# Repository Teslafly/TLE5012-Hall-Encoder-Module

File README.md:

# TLE5012-Hall-Encoder-Module
Breakout/mounting board for the TLE5012 hall encoder to use with the vesc motor controller project.

(Pictures are from my nearly identical as5047 encoder board at https://github.com/Teslafly/AS5047-Hall-Encoder-Module)

# Mounting:
- The mounting holes fit an m3 screw and are 16mm apart center to center.
- If the pcb cannot recess into the motor, a 3d printed shim (file link) can raise the encoder and provide clearance. If the motor gets too hot, the shim may be laser cut or milled out of a more resistant material.
- This encoder works with a diametric magnet fixed to the motor shaft. 
    - The magnet must be centered on the shaft. The encoder must be centered over the center of the magnet.
    - I find good results with a 6x2mm or 6x3mm neodymium magnet placed 1-5mm away from the face of the encoder.
    - Magnet example: https://www.aliexpress.us/item/3256801356246959.html

# Building:
- This pcb can be hand soldered easially.
- You can use either horizontal or vertical jst gh connectors for each connector placement. The vertical data connector should be placed with pins outwards to maintain the same pinout between the horizontal/vertical data connector options.
- As the temperature sensor connector is unpolarised, either horizontal or vertical connector can be placed on the same footprint. see pictures.

# JST GH mating connectors and making cables:
- If you do not have a crimper for JST GH crimps, they are fiddley and are hard to crimp properly.
I recommend either getting a male to male JST GH cable and cutting it to splice into a longer encoder cable, or doing the same with a precrimped silicone wire kit like this:
  - https://www.amazon.com/Pre-Crimped-Connectors-Pixhawk2-Pixracer-Silicone/dp/B07PBHN7TM/
  - Silicone wire is preferred due to it's durability and heat resistance. If you use pvc wire you should reinforce around the male GH connector with silocone rtv.

- The jst gh data connector has the same pinout as the JST PH vesc hall sensor connector.
however, note that some vesc hardwares that have swapped to JST GH connectors have reversed pinouts.
aka the cable must connect pins 1<->6, 2<->5, etc so that the locking clips are reversed from each other.
  - THIS IS NOT THE CASE ON ALL HARDWARES. CHECK YOUR PINOUT BEFORE POWERING.
    A REVERSED PINOUT WILL DESTROY THE ENCODER AS 5V AND GND ARE SWAPPED.
  - (The sensor should get lukewarm during operation. If it gets really hot then it's dead or a wire is shorted)

- Also, your vesc hardware must not have filters placed on the hall port pins. 
these filters must be removed for this encoder to work if present. They are present on all vesc hw 4.2, and nearly all flipsky boards. Trampa hw 6.0+ do not have these filters and will work as is.

### Wire:
I recommend using sheilded wire. usb cable will work in a pinch if you omot the temp wire and use the sheild for gnd. but ~28awg 6 core sheilded cable is ideal. the sheild should be connected to the gnd pin on the vesc side, and unconnected on the sensor side. you must keep all wires close to each other to get good signal integrity when splicing /crimping the end connectors.
If you cannot source sheilded wire, you will get acceptable results by keeping the wires close, and routing the cable away from the phase wires of the motor.
It is recommended that the data cable is kept under 0.5 meters. If that is not possible then sheilded wire must be used and attention to detail excercised in cable construction.

# Testing:
- This sensor runs best at 5V input power. 3.3V operation is not gaurenteed but will not cause damage.
- The led on the pcb should glow somewhat dimly. It is not blindingly bright.
- The sensor IC should get lukewarm during operation. If it gets really hot then it's dead or a wire is shorted

- You can troubleshoot/test the signal integrity of your cable and encoder functionality with the "`encoder`" command in the vesc terminal. 
  - The error rate should be very close to zero.
  - If it is above 0.5% then you should troubleshoot your setup and improve signal integrity. 
  - 99+% generally means that all communication with the encoder has failed. The wiring may be wrong, the sensor dead, or your vesc has hall port filters that need to be removed and shorted.
- when viewing the encoder angle in the vest-tool realtime view, the encoder value should change smoothly through the entire 360 degrees. If it is jumpy you probably have a signal integrity issue
- If the sensor cable is poorly routed/sheilded, high motor currents can cause noise that increases the encoder error rate. If you experience encoder faults during acceleration, check for intermittent opens in all signals and try rerouting the sensor cable away from motor phase wires and battery cables.
- a 3d printable test jig using a 608 bearing and 6mm magnet is included in the "`608 bearing test holder`" folder.

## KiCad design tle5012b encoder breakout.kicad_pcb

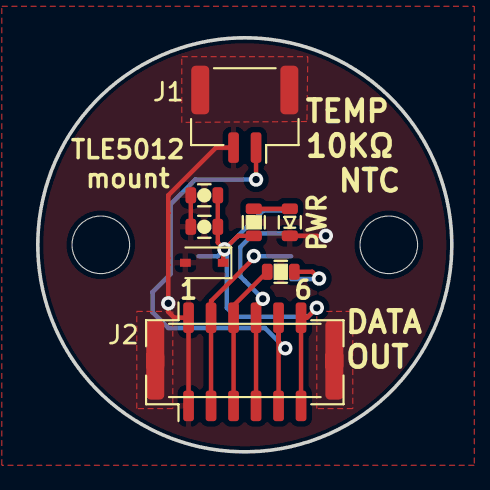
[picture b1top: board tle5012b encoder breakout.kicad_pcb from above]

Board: 2 copper layers, 23.0 x 23.0 mm, 12 parts (1 on the bottom side), 8 nets.

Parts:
C1: 1uf; C_0603
C2: 4.7uf; C_0603
D1: GREEN LED; D_0603
D2: SD05-01FTG; D_SOD-323
H1, H2: MountingHole; MountingHole_3.2mm_M3
J1: Conn_01x02; JST_GH_SM02B-GHS-TB_1x02-1MP_P1.25mm_Horizontal
J2: data-V; JST_GH_BM06B-GHS-TBT_1x06-1MP_P1.25mm_Vertical
J3: data-H; JST_GH_SM06B-GHS-TB_1x06-1MP_P1.25mm_Horizontal
R1: 10k; R_0603
R2: 470R; R_0603
U1: TLE5012; SO-8_3.9x4.9mm_P1.27mm

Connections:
+5V: C1.1, C2.1, D2.1 (K), J2.6, J3.6, R1.1, U1.6 (VDD)
/H1/SCK: J2.4, J3.4, U1.2 (SCK)
/H2/SSC_DATA: J2.3, J3.3, R2.1
/H3/CS: J2.2, J3.2, U1.3 (CSQ)
/Temp: J1.1, J2.5, J3.5
GND: C1.2, C2.2, D1.C (K), D2.2 (A), J1.2, J1.MP, J2.1, J2.MP, J3.1, J3.MP, U1.7 (GND)
unnamed: D1.A, R1.2
unnamed: R2.2, U1.4 (DATA)

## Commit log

2022-01-20 Initial commit of v1
2022-12-06 add pictures for readme
2022-12-06 add 3d printed test jig files
2022-12-06 Add pictures and instructions to readme.
2022-12-06 fix picture links
2022-12-07 update kicad version
2022-12-07 update schematic picture
2022-12-07 Connected connector mounting pads to gnd plane for structural support
2022-12-15 Update README.md
    add link to other board
